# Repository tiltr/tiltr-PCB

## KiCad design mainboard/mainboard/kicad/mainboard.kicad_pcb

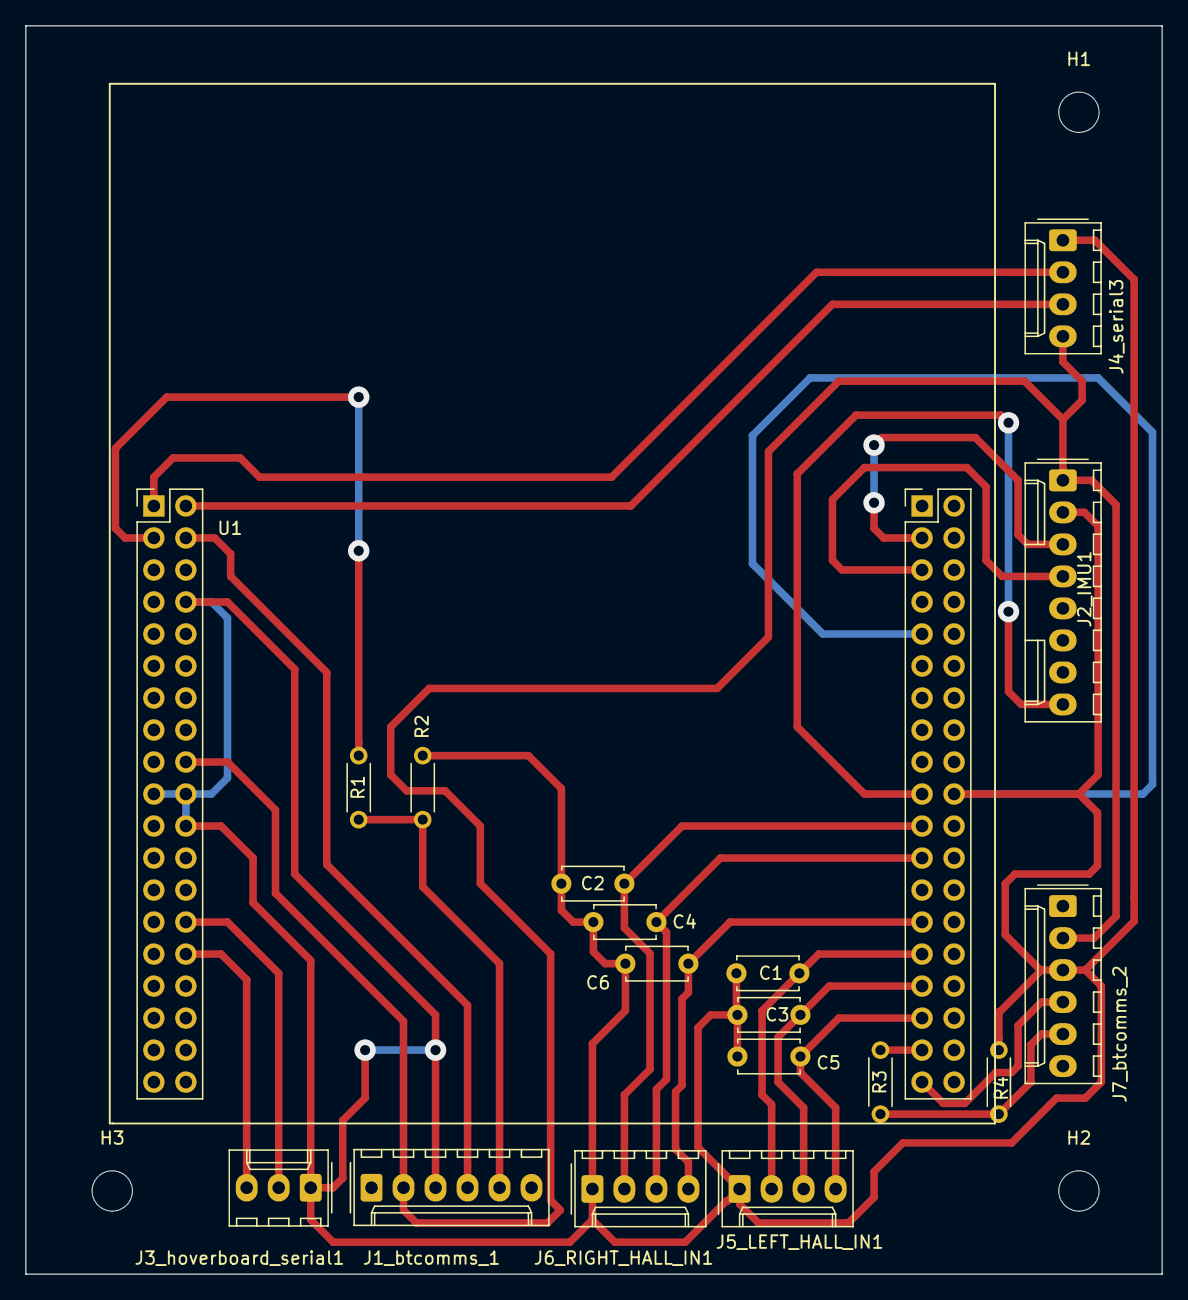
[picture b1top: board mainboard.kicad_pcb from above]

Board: 2 copper layers, 90.2 x 99.1 mm, 21 parts (0 on the bottom side), 21 nets.

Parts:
C1, C2, C3, C4, C5, C6: 5nF; C_Disc_D4.7mm_W2.5mm_P5.00mm
H1, H2, H3: MountingHole; MountingHole_3.2mm_M3
J1_btcomms_1, J7_btcomms_2: Conn_01x06; Molex_KK-254_AE-6410-06A_1x06_P2.54mm_Vertical
J2_IMU1: Conn_01x08; Molex_KK-254_AE-6410-08A_1x08_P2.54mm_Vertical
J3_hoverboard_serial1: Conn_01x03; Molex_KK-254_AE-6410-03A_1x03_P2.54mm_Vertical
J4_serial3, J5_LEFT_HALL_IN1, J6_RIGHT_HALL_IN1: Conn_01x04; Molex_KK-254_AE-6410-04A_1x04_P2.54mm_Vertical
R1, R3: 1k; R_Axial_DIN0204_L3.6mm_D1.6mm_P5.08mm_Horizontal
R2, R4: 2k; R_Axial_DIN0204_L3.6mm_D1.6mm_P5.08mm_Horizontal
U1: STM32F446RETx; NUCLEO_F446RE

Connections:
+5V: J1_btcomms_1.2, J2_IMU1.1, J4_serial3.4, J7_btcomms_2.2, U1.5V
GND: C1.2, C2.2, C3.2, C4.2, C5.2, C6.2, J1_btcomms_1.3, J2_IMU1.2, J3_hoverboard_serial1.1, J4_serial3.1, J5_LEFT_HALL_IN1.1, J6_RIGHT_HALL_IN1.1, J7_btcomms_2.3, R2.1, R4.1, U1.GND
IMU_INT: J2_IMU1.8, U1.PC7
IMU_SCL: J2_IMU1.3, U1.PB8
IMU_SDA: J2_IMU1.4, U1.PB9
L_hall_A_LPF: C5.1, J5_LEFT_HALL_IN1.4, U1.PA10
L_hall_B_LPF: C3.1, J5_LEFT_HALL_IN1.3, U1.PB3
L_hall_C_LPF: C1.1, J5_LEFT_HALL_IN1.2, U1.PB5
unnamed: J1_btcomms_1.5, R1.2, R2.2
unnamed: J7_btcomms_2.5, R3.2, R4.2
R_hall_A_LPF: C6.1, J6_RIGHT_HALL_IN1.4, U1.PB4
R_hall_B_LPF: C4.1, J6_RIGHT_HALL_IN1.3, U1.PA8
R_hall_C_LPF: C2.1, J6_RIGHT_HALL_IN1.2, U1.PA9
bluetooth_serial_1_Rx: R1.1, U1.PC12
bluetooth_serial_1_Tx: J1_btcomms_1.4, U1.PD2
bluetooth_serial_2_Rx: R3.1, U1.PA2
bluetooth_serial_2_Tx: J7_btcomms_2.4, U1.PA3
hoverboard_serial_Rx: J3_hoverboard_serial1.2, U1.PA0
hoverboard_serial_Tx: J3_hoverboard_serial1.3, U1.PA1
serial3_Rx: J4_serial3.2, U1.PC10
serial3_Tx: J4_serial3.3, U1.PC11

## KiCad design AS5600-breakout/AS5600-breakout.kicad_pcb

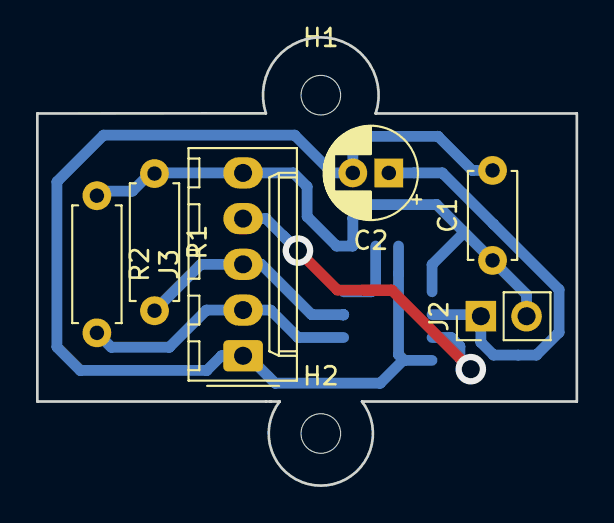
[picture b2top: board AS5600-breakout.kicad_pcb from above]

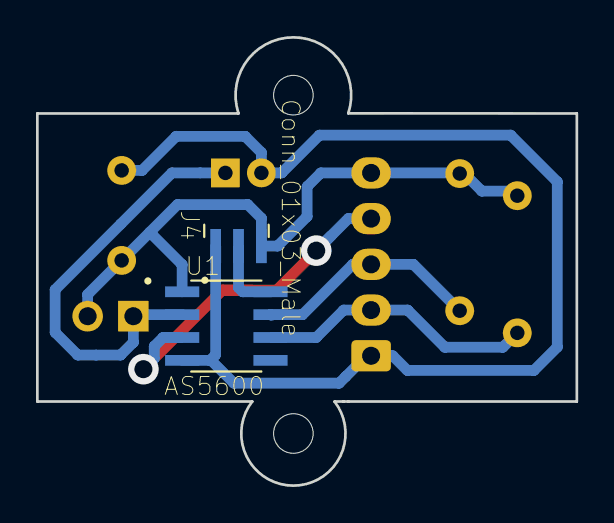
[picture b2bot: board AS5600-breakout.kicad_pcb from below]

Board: 2 copper layers, 30.0 x 24.9 mm, 10 parts (2 on the bottom side), 7 nets.

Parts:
C1: 100nF; C_Disc_D4.7mm_W2.5mm_P5.00mm
C2: 1uF; CP_Radial_D5.0mm_P2.00mm
H1, H2: MountingHole; MountingHole_2.2mm_M2_small
J2: Conn_01x02; PinHeader_1x02_P2.54mm_Vertical
J3: Conn_01x05_Female; Molex_KK-254_AE-6410-05A_1x05_P2.54mm_Vertical
J4: Conn_01x03_Male; SOIC127_solder_switch
R1, R2: 4.7k; R_Axial_DIN0207_L6.3mm_D2.5mm_P7.62mm_Horizontal
U1: AS5600; SOIC127P600X175-8N

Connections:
+5V: C1.1, J2.2, J3.5, J4.3, R1.1, R2.1, U1.1
DIR: J4.2, U1.8
GND: C1.2, C2.2, J3.1, J4.1, U1.4
unnamed: C2.1, J2.1, U1.2
OUT: J3.4, U1.3
SCL: J3.3, R1.2, U1.7
SDA: J3.2, R2.2, U1.6

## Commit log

2019-08-11 porting PCBs from old repo
2019-09-21 start of nucleo breakout (including serial and low pass filters)
2019-09-22 started routing, added 5v
2019-09-27 routed, checking...
2019-09-28 ready for first cut
2019-10-03 added output files, cleaned up
2019-10-08 removed 'home once finished' from gcode
